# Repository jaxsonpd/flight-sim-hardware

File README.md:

# Flight Sim Hardware

Hardware for the MSFS2020 flight sim.

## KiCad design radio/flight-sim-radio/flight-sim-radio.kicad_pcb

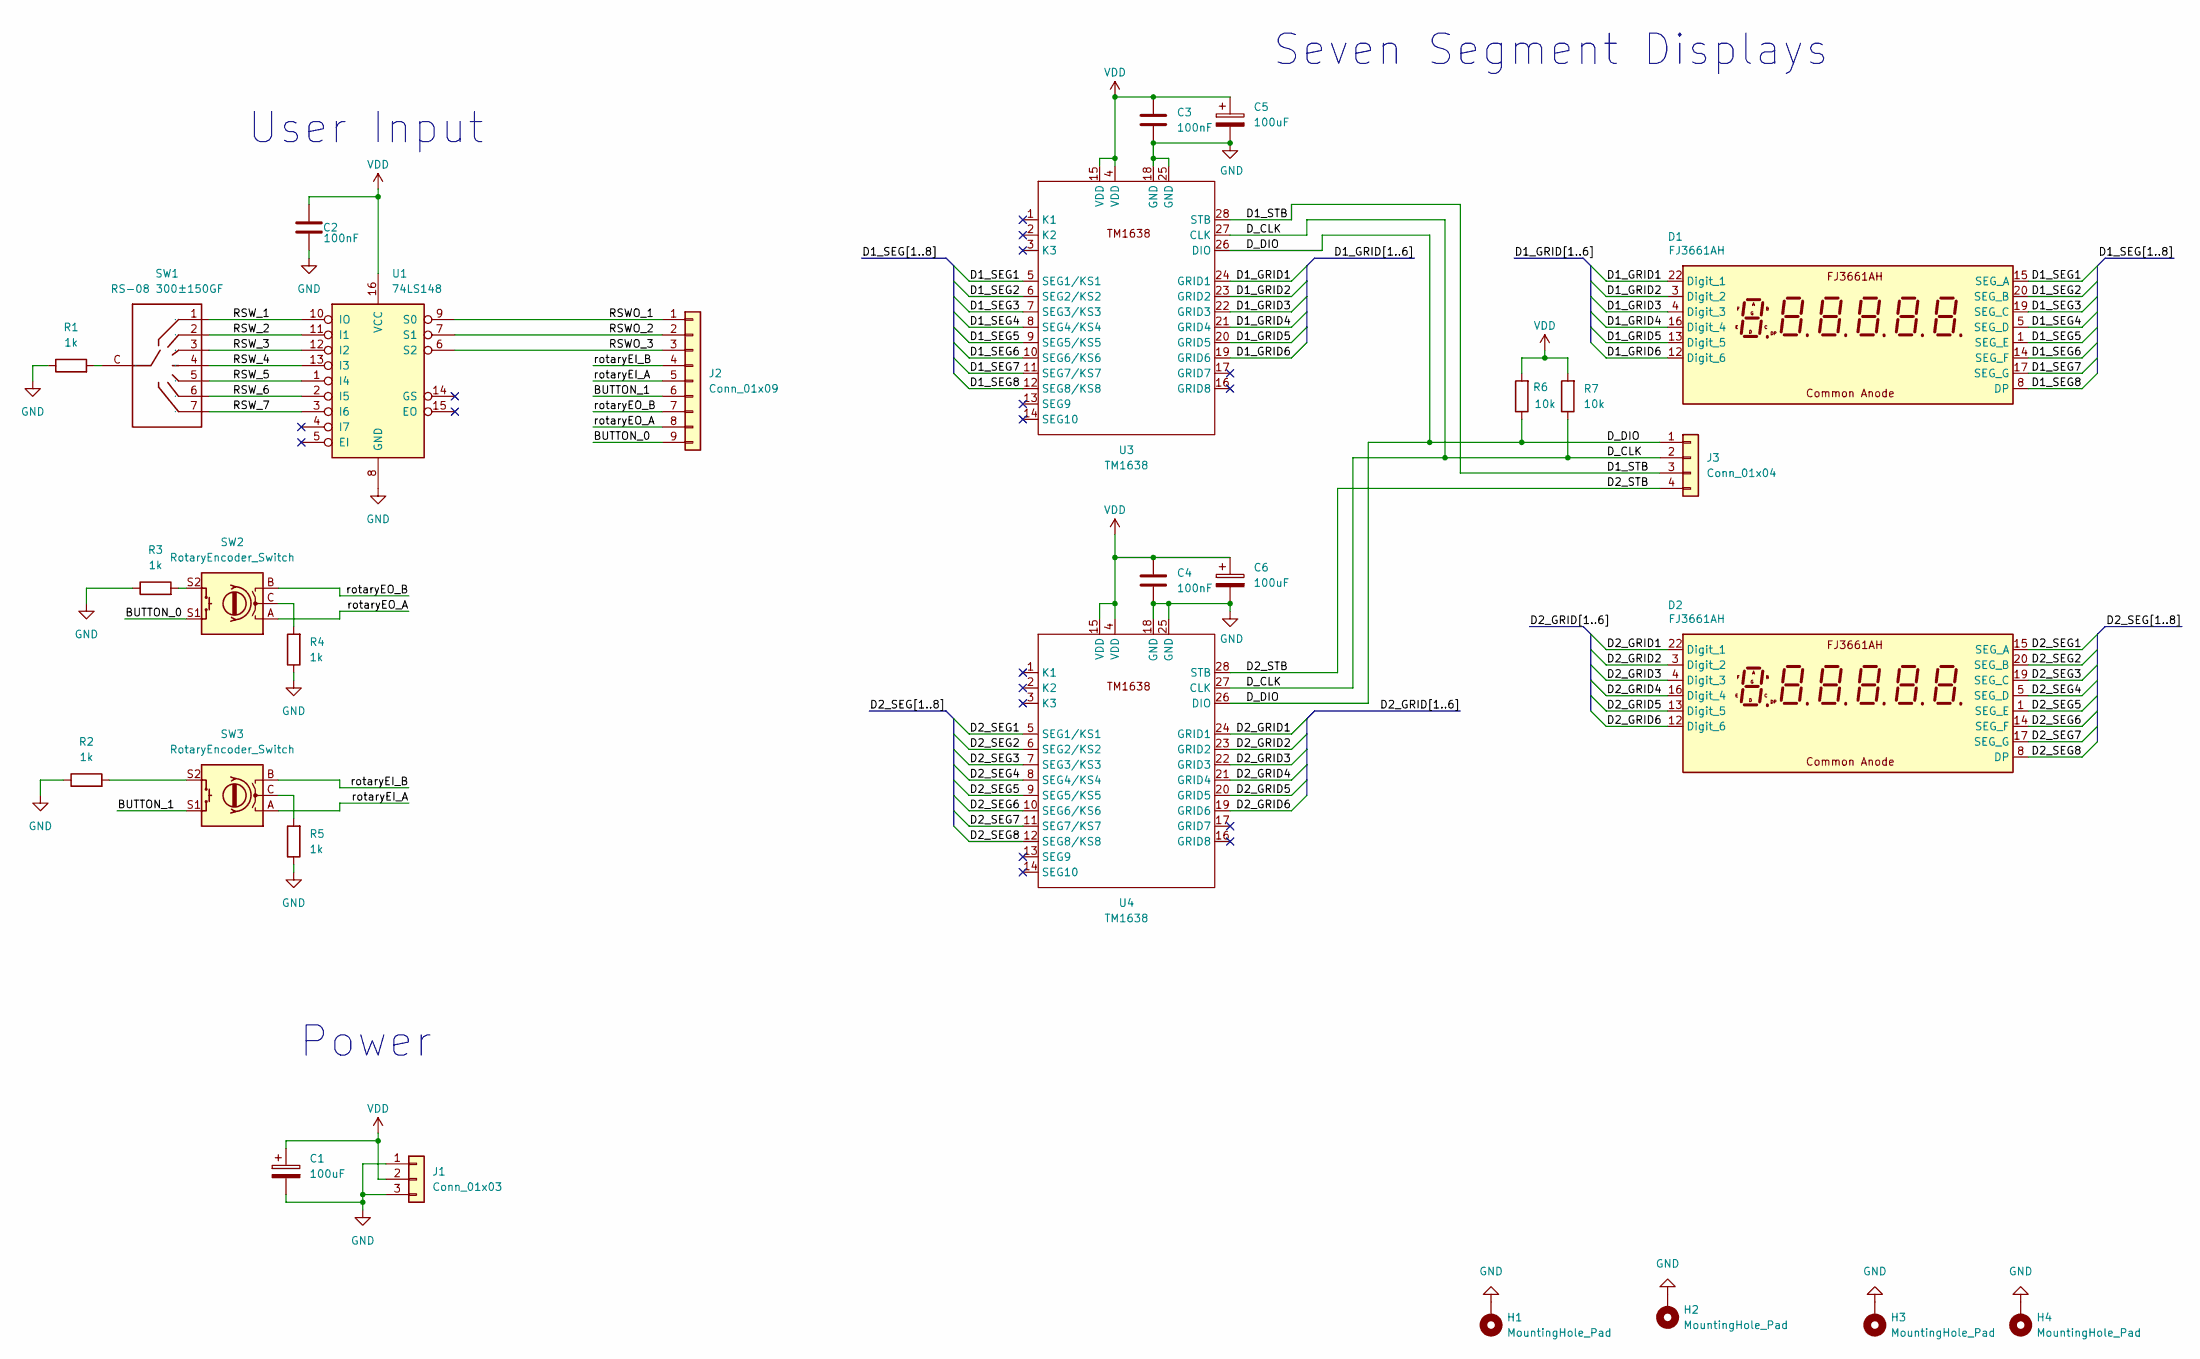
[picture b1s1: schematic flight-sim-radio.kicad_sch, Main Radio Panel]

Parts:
C1, C5, C6: 100uF; CP_Radial_D4.0mm_P2.00mm
C2, C3, C4: 100nF; C_Disc_D5.0mm_W2.5mm_P2.50mm
D1, D2: FJ3661AH; FJ3661AH-DIP22
H1, H2, H3, H4: MountingHole_Pad; MountingHole_2.7mm_M2.5_Pad
J1: Conn_01x03; PinHeader_1x03_P2.54mm_Vertical
J2: Conn_01x09; PinHeader_1x09_P2.54mm_Vertical
J3: Conn_01x04; PinHeader_1x04_P2.54mm_Vertical
R1, R2, R3, R4, R5: 1k; R_Axial_DIN0207_L6.3mm_D2.5mm_P10.16mm_Horizontal
R6, R7: 10k; R_Axial_DIN0207_L6.3mm_D2.5mm_P10.16mm_Horizontal
SW1: RS-08 300±150GF; SW-TH_RS-08-300-150GF; Manufacturer Part RS-08 300±150gf
SW2, SW3: RotaryEncoder_Switch; ALPSALPINE EC11E09444A8
U1: 74LS148; DIP-16_W7.62mm
U3, U4: TM1638

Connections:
/BUTTON_0: J2.9, SW2.S1
/BUTTON_1: J2.6, SW3.S1
/D1_GRID1: D1.22 (Digit_1), U3.24 (GRID1)
/D1_GRID2: D1.3 (Digit_2), U3.23 (GRID2)
/D1_GRID3: D1.4 (Digit_3), U3.22 (GRID3)
/D1_GRID4: D1.16 (Digit_4), U3.21 (GRID4)
/D1_GRID5: D1.13 (Digit_5), U3.20 (GRID5)
/D1_GRID6: D1.12 (Digit_6), U3.19 (GRID6)
/D1_SEG1: D1.15 (SEG_A), U3.5 (SEG1/KS1)
/D1_SEG2: D1.20 (SEG_B), U3.6 (SEG2/KS2)
/D1_SEG3: D1.19 (SEG_C), U3.7 (SEG3/KS3)
/D1_SEG4: D1.5 (SEG_D), U3.8 (SEG4/KS4)
/D1_SEG5: D1.1 (SEG_E), U3.9 (SEG5/KS5)
/D1_SEG6: D1.14 (SEG_F), U3.10 (SEG6/KS6)
/D1_SEG7: D1.17 (SEG_G), U3.11 (SEG7/KS7)
/D1_SEG8: D1.8 (DP), U3.12 (SEG8/KS8)
/D1_STB: J3.3, U3.28 (STB)
/D2_GRID1: D2.22 (Digit_1), U4.24 (GRID1)
/D2_GRID2: D2.3 (Digit_2), U4.23 (GRID2)
/D2_GRID3: D2.4 (Digit_3), U4.22 (GRID3)
/D2_GRID4: D2.16 (Digit_4), U4.21 (GRID4)
/D2_GRID5: D2.13 (Digit_5), U4.20 (GRID5)
/D2_GRID6: D2.12 (Digit_6), U4.19 (GRID6)
/D2_SEG1: D2.15 (SEG_A), U4.5 (SEG1/KS1)
/D2_SEG2: D2.20 (SEG_B), U4.6 (SEG2/KS2)
/D2_SEG3: D2.19 (SEG_C), U4.7 (SEG3/KS3)
/D2_SEG4: D2.5 (SEG_D), U4.8 (SEG4/KS4)
/D2_SEG5: D2.1 (SEG_E), U4.9 (SEG5/KS5)
/D2_SEG6: D2.14 (SEG_F), U4.10 (SEG6/KS6)
/D2_SEG7: D2.17 (SEG_G), U4.11 (SEG7/KS7)
/D2_SEG8: D2.8 (DP), U4.12 (SEG8/KS8)
/D2_STB: J3.4, U4.28 (STB)
/D_CLK: J3.2, R7.1, U3.27 (CLK), U4.27 (CLK)
/D_DIO: J3.1, R6.1, U3.26 (DIO), U4.26 (DIO)
/RSWO_1: J2.1, U1.9 (S0)
/RSWO_2: J2.2, U1.7 (S1)
/RSWO_3: J2.3, U1.6 (S2)
/RSW_1: SW1.1, U1.10 (IO)
/RSW_2: SW1.2, U1.11 (I1)
/RSW_3: SW1.3, U1.12 (I2)
/RSW_4: SW1.4, U1.13 (I3)
/RSW_5: SW1.5, U1.1 (I4)
/RSW_6: SW1.6, U1.2 (I5)
/RSW_7: SW1.7, U1.3 (I6)
/rotaryEI_A: J2.5, SW3.A
/rotaryEI_B: J2.4, SW3.B
/rotaryEO_A: J2.8, SW2.A
/rotaryEO_B: J2.7, SW2.B
GND: C1.2, C2.1, C3.2, C4.2, C5.2, C6.2, H1.1, H2.1, H3.1, H4.1, J1.1, J1.3, R1.1, R2.1, R3.1, R4.1, R5.1, U1.8 (GND), U3.18 (GND), U3.25 (GND), U4.18 (GND), U4.25 (GND)
unnamed: R1.2, SW1.C
unnamed: R2.2, SW3.S2
unnamed: R3.2, SW2.S2
unnamed: R4.2, SW2.C
unnamed: R5.2, SW3.C
VDD: C1.1, C2.2, C3.1, C4.1, C5.1, C6.1, J1.2, R6.2, R7.2, U1.16 (VCC), U3.4 (VDD), U3.15 (VDD), U4.4 (VDD), U4.15 (VDD)

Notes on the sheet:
Power
User Input
Seven Segment Displays

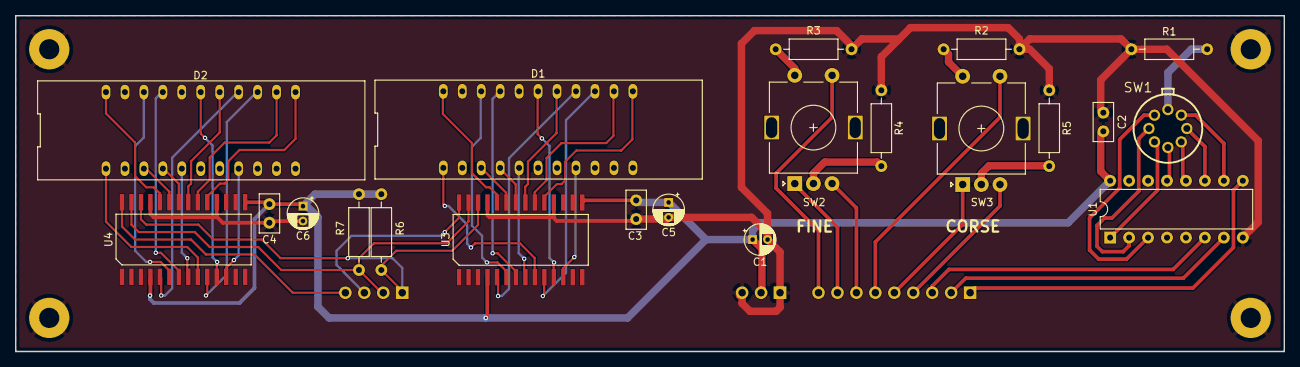
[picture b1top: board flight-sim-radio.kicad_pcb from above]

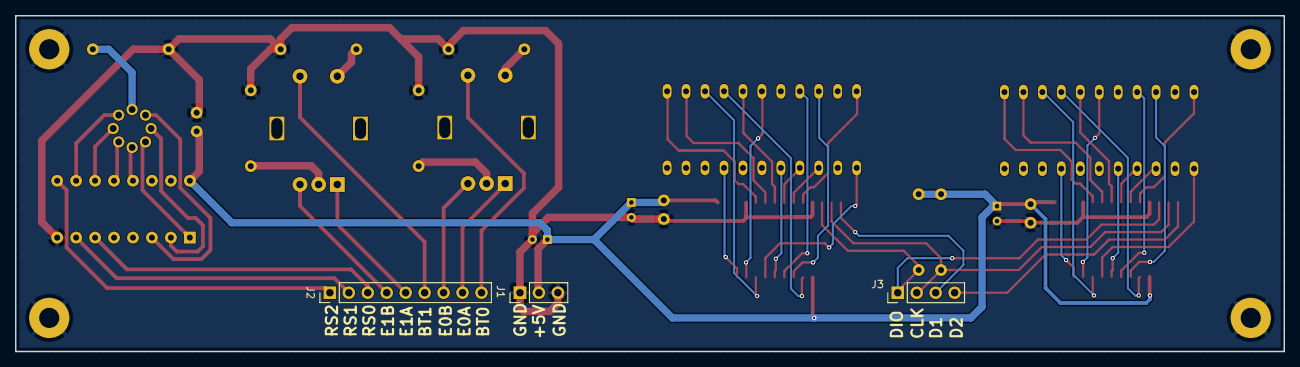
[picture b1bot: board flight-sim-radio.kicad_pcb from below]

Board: 2 copper layers, 170.0 x 45.0 mm, 28 parts (3 on the bottom side), 55 nets.

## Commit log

2024-11-30 Python driver MVP working
2024-11-30 Sketch created
2024-11-30 MVP firmware working
2024-11-30 Coms working
2024-12-01 linux arduino setup
2024-12-01 componets added
2024-12-01 Updated string formating
2024-12-01 seven segment display working
2024-12-01 Multisegment written
2024-12-01 CHanged multi update function
2024-12-03 Fixed digit extraction
2024-12-03 multi segment display working
2024-12-03 displaying from serial
2024-12-03 Kicad Project Created
2024-12-03 Started on schematic
2024-12-05 LED driver added
2024-12-05 LED driver wired
2024-12-08 7 segement display outlined
2024-12-15 Schematic Draft finished
2024-12-15 Preliminary layout and design rules added
2024-12-16 7 segment display created (wrong)
2024-12-17 7 Segment Models created
2024-12-17 More PCB updates
2024-12-22 input layed out
2024-12-22 PCB routing done
2024-12-22 Fixed PCB Errors
2024-12-23 Quadrature encoder model started
2024-12-24 PCB routing updated
2024-12-24 PCB checked
2024-12-24 PCB ready for manufacturing
2024-12-24 Cleaned up structure
2025-01-26 Cleanup repo
2025-01-26 Added TM1368 symbol
2025-01-26 Added new driver to schematic
2025-01-26 First driver layed out
2025-02-18 PCB complete
2025-02-18 Update silk screen
2025-02-18 Ready for production
2025-03-10 Started on mechanical design
2025-03-11 Face plate started
2025-05-12 Next version of radio front complete need to lengthen standoffs
2025-05-14 Increased standoff size on the front panel
2025-06-10 Cleanup radio mechanical
2025-06-10 Created flatbed version and exported it
